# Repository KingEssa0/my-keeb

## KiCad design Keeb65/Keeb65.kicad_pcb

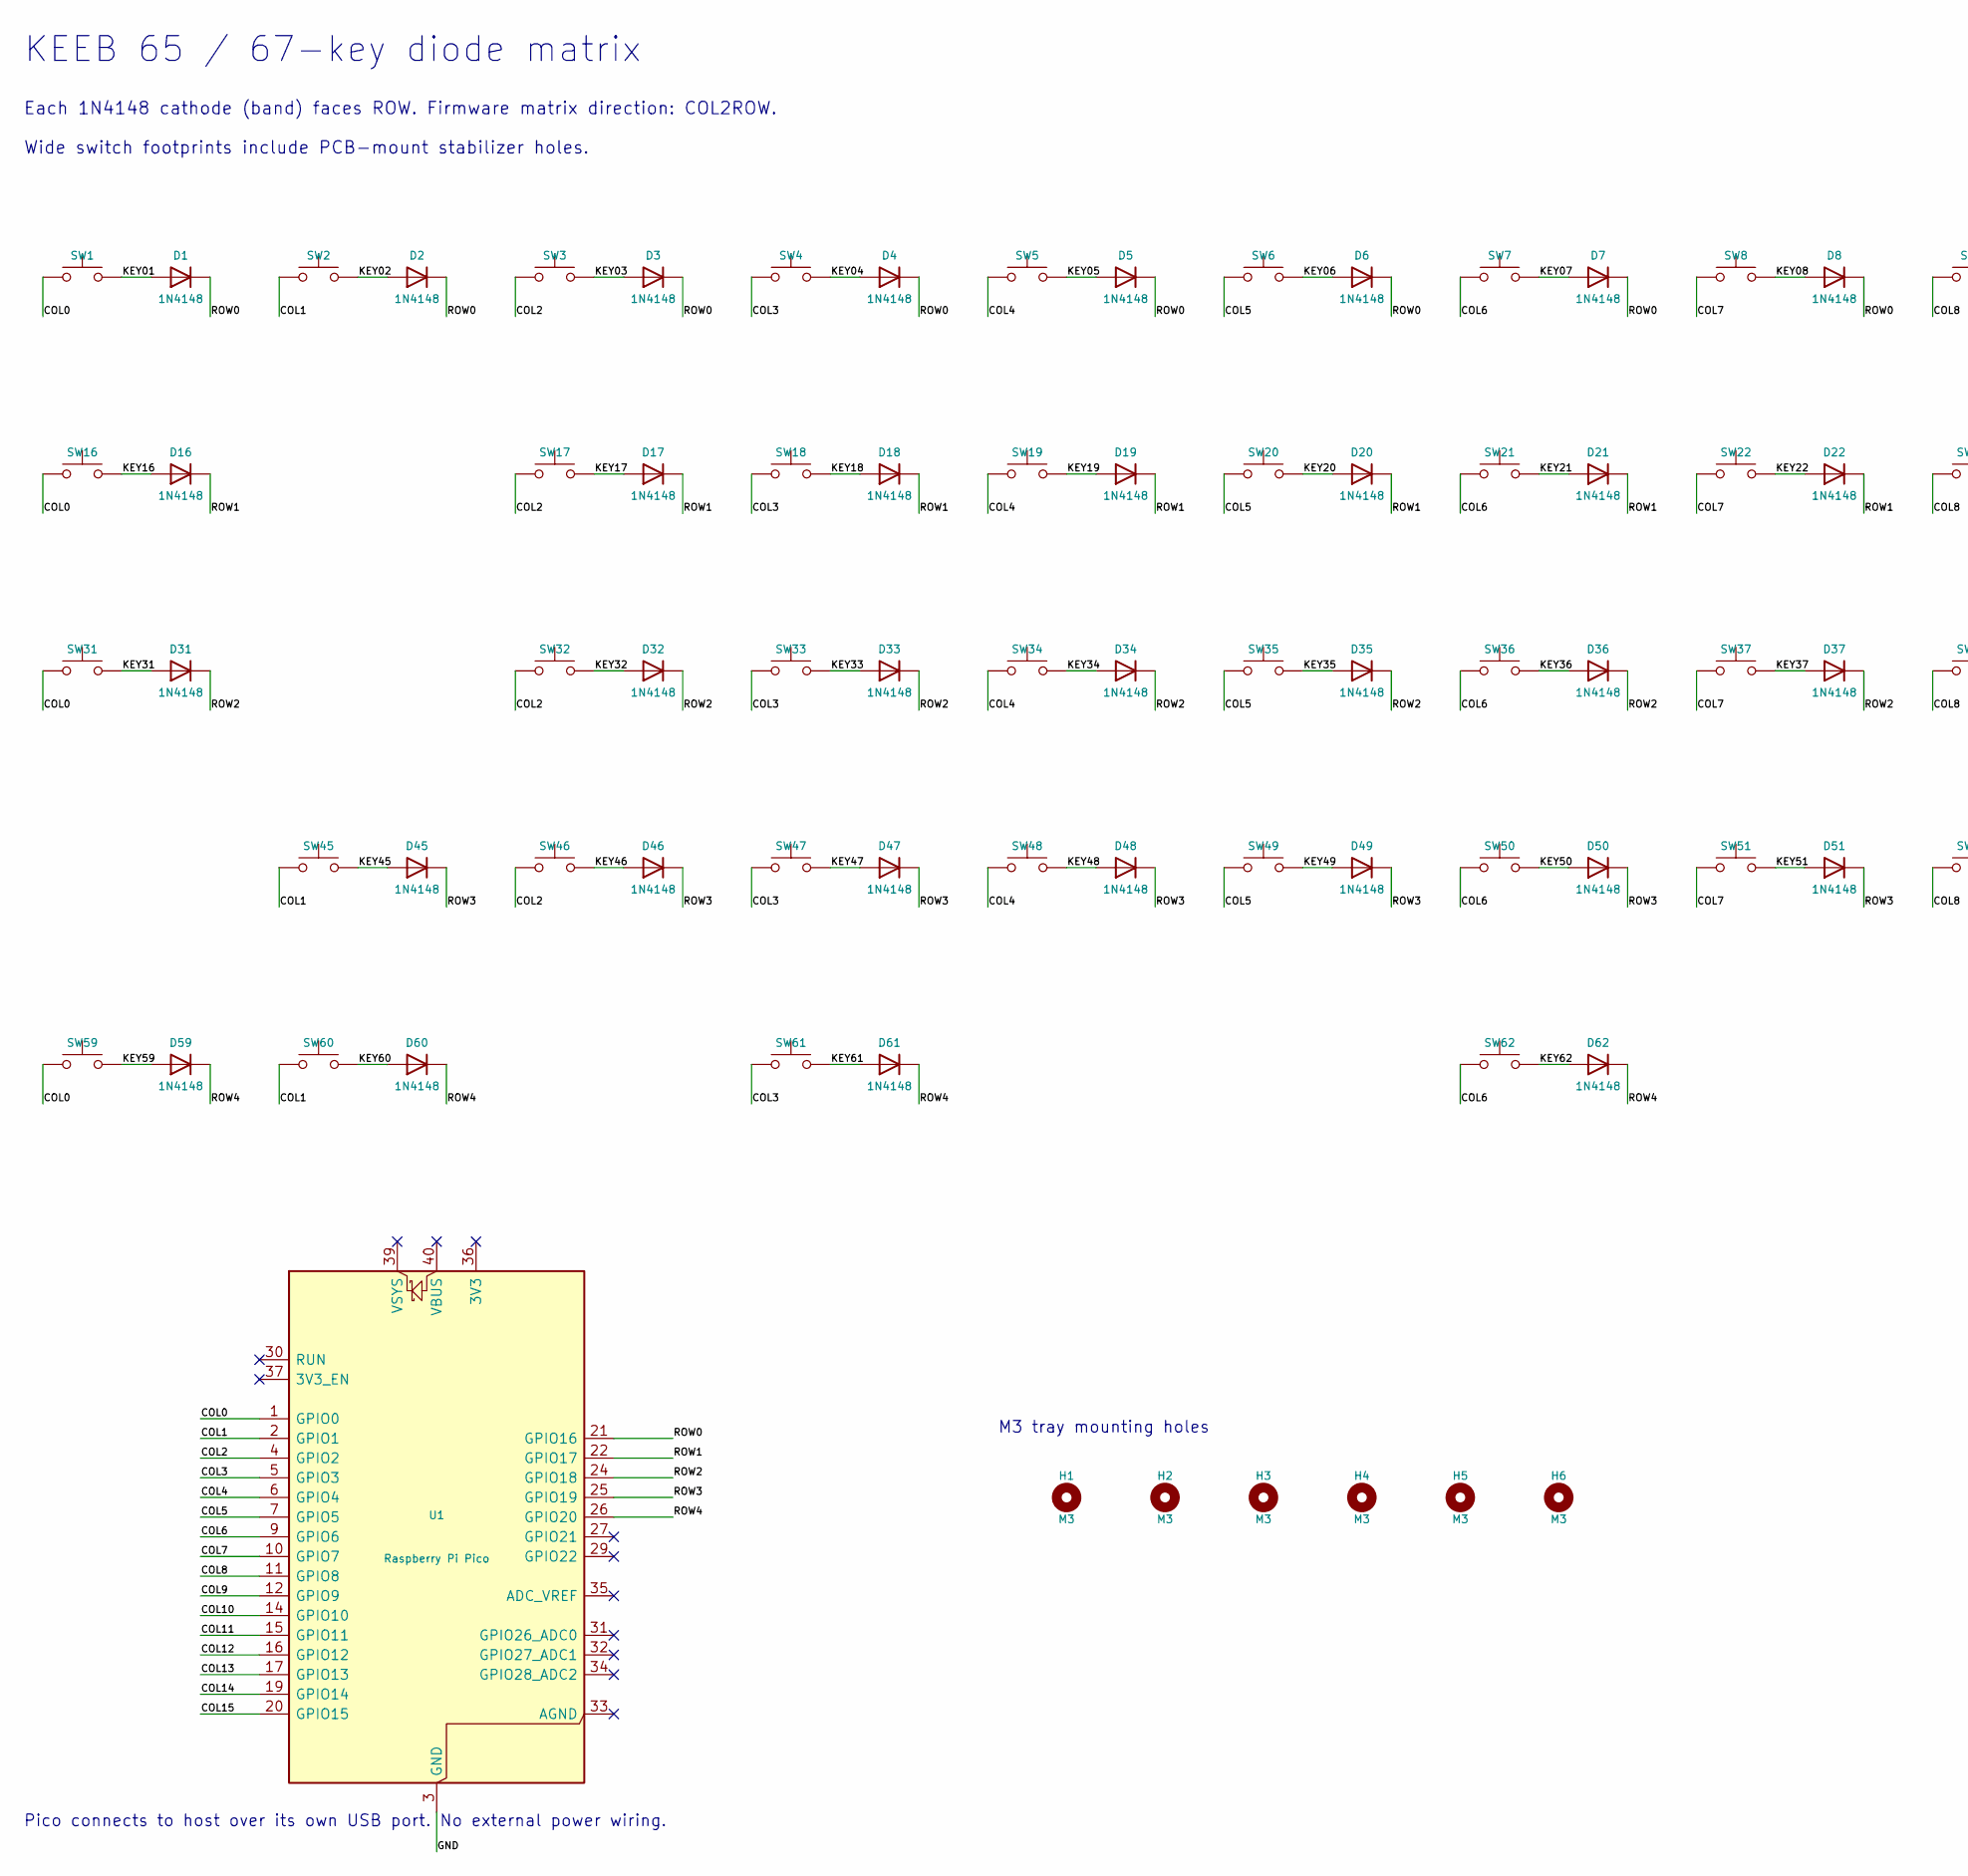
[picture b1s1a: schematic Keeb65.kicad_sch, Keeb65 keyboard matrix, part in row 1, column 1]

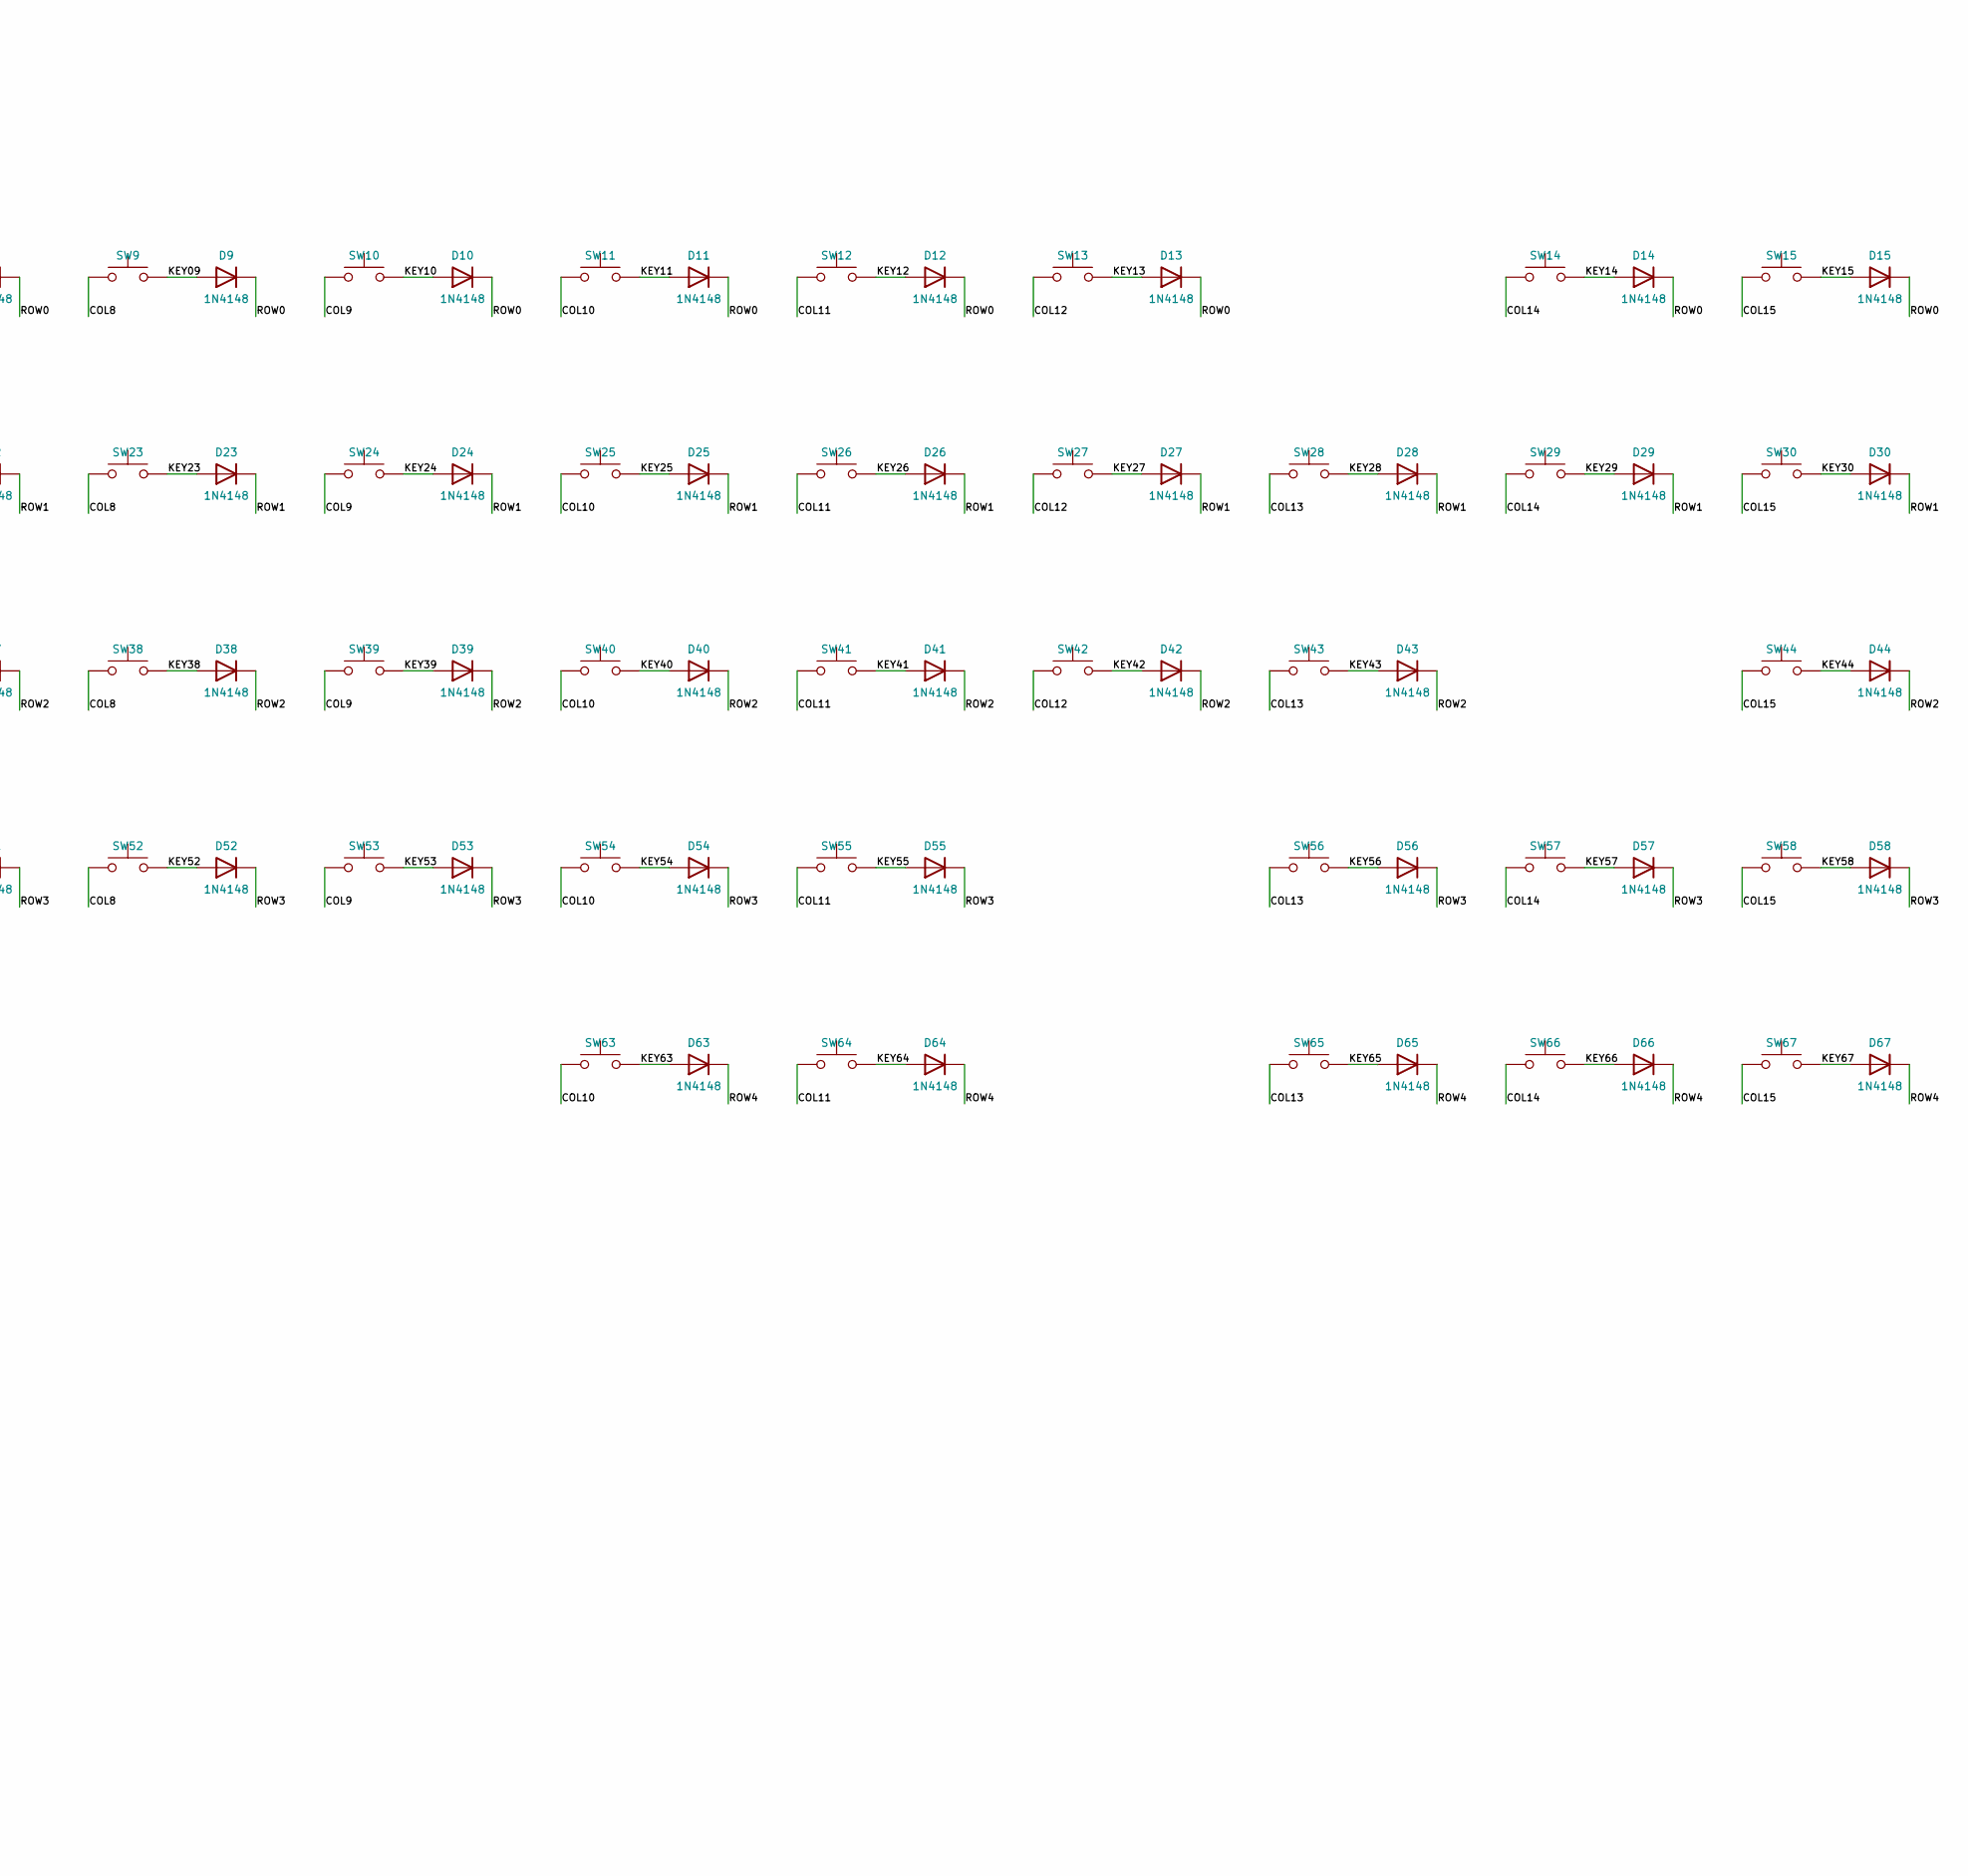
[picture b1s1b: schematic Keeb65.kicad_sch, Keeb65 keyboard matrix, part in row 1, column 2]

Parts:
D1, D2, D3, D4, D5, D6, D7, D8, D9, D10, D11, D12, D13, D14, D15, D16, D17, D18, D19, D20, D21, D22, D23, D24, D25, D26, D27, D28, D29, D30, D31, D32, D33, D34, D35, D36, D37, D38, D39, D40, D41, D42, D43, D44, D45, D46, D47, D48, D49, D50, D51, D52, D53, D54, D55, D56, D57, D58, D59, D60, D61, D62, D63, D64, D65, D66, D67: 1N4148; D_DO-35_SOD27_P7.62mm_Horizontal
H1, H2, H3, H4, H5, H6: M3; MountingHole_3.2mm_M3
SW1: Esc; SW_Cherry_MX_1.00u_PCB
SW2: 1; SW_Cherry_MX_1.00u_PCB
SW3: 2; SW_Cherry_MX_1.00u_PCB
SW4: 3; SW_Cherry_MX_1.00u_PCB
SW5: 4; SW_Cherry_MX_1.00u_PCB
SW6: 5; SW_Cherry_MX_1.00u_PCB
SW7: 6; SW_Cherry_MX_1.00u_PCB
SW8: 7; SW_Cherry_MX_1.00u_PCB
SW9: 8; SW_Cherry_MX_1.00u_PCB
SW10: 9; SW_Cherry_MX_1.00u_PCB
SW11: 0; SW_Cherry_MX_1.00u_PCB
SW12: -; SW_Cherry_MX_1.00u_PCB
SW13: =; SW_Cherry_MX_1.00u_PCB
SW14: Backspace; SW_Cherry_MX_2.00u_PCB
SW15: Del; SW_Cherry_MX_1.00u_PCB
SW16: Tab; SW_Cherry_MX_1.00u_PCB
SW17: Q; SW_Cherry_MX_1.00u_PCB
SW18: W; SW_Cherry_MX_1.00u_PCB
SW19: E; SW_Cherry_MX_1.00u_PCB
SW20: R; SW_Cherry_MX_1.00u_PCB
SW21: T; SW_Cherry_MX_1.00u_PCB
SW22: Y; SW_Cherry_MX_1.00u_PCB
SW23: U; SW_Cherry_MX_1.00u_PCB
SW24: I; SW_Cherry_MX_1.00u_PCB
SW25: O; SW_Cherry_MX_1.00u_PCB
SW26: P; SW_Cherry_MX_1.00u_PCB
SW27: [; SW_Cherry_MX_1.00u_PCB
SW28: ]; SW_Cherry_MX_1.00u_PCB
SW29: \; SW_Cherry_MX_1.00u_PCB
SW30: PgUp; SW_Cherry_MX_1.00u_PCB
SW31: Caps; SW_Cherry_MX_1.00u_PCB
SW32: A; SW_Cherry_MX_1.00u_PCB
SW33: S; SW_Cherry_MX_1.00u_PCB
SW34: D; SW_Cherry_MX_1.00u_PCB
SW35: F; SW_Cherry_MX_1.00u_PCB
SW36: G; SW_Cherry_MX_1.00u_PCB
SW37: H; SW_Cherry_MX_1.00u_PCB
SW38: J; SW_Cherry_MX_1.00u_PCB
SW39: K; SW_Cherry_MX_1.00u_PCB
SW40: L; SW_Cherry_MX_1.00u_PCB
SW41: ;; SW_Cherry_MX_1.00u_PCB
SW42: '; SW_Cherry_MX_1.00u_PCB
SW43: Enter; SW_Cherry_MX_2.25u_PCB
SW44: PgDn; SW_Cherry_MX_1.00u_PCB
SW45: LShift; SW_Cherry_MX_2.25u_PCB
SW46: Z; SW_Cherry_MX_1.00u_PCB
SW47: X; SW_Cherry_MX_1.00u_PCB
SW48: C; SW_Cherry_MX_1.00u_PCB
SW49: V; SW_Cherry_MX_1.00u_PCB
SW50: B; SW_Cherry_MX_1.00u_PCB
SW51: N; SW_Cherry_MX_1.00u_PCB
SW52: M; SW_Cherry_MX_1.00u_PCB
SW53: ,; SW_Cherry_MX_1.00u_PCB
SW54: .; SW_Cherry_MX_1.00u_PCB
SW55: /; SW_Cherry_MX_1.00u_PCB
SW56: RShift; SW_Cherry_MX_1.00u_PCB
SW57: Up; SW_Cherry_MX_1.00u_PCB
SW58: End; SW_Cherry_MX_1.00u_PCB
SW59: LCtrl; SW_Cherry_MX_1.00u_PCB
SW60: Win; SW_Cherry_MX_1.00u_PCB
SW61: LAlt; SW_Cherry_MX_1.00u_PCB
SW62: Space; SW_Cherry_MX_6.25u_PCB
SW63: RAlt; SW_Cherry_MX_1.00u_PCB
SW64: Fn; SW_Cherry_MX_1.00u_PCB
SW65: Left; SW_Cherry_MX_1.00u_PCB
SW66: Down; SW_Cherry_MX_1.00u_PCB
SW67: Right; SW_Cherry_MX_1.00u_PCB
U1: Raspberry Pi Pico; RaspberryPi_Pico_RightEdge_THT

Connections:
/COL0: SW1.1, SW16.1, SW31.1, SW59.1, U1.1 (GPIO0)
/COL1: SW2.1, SW45.1, SW60.1, U1.2 (GPIO1)
/COL2: SW3.1, SW17.1, SW32.1, SW46.1, U1.4 (GPIO2)
/COL3: SW4.1, SW18.1, SW33.1, SW47.1, SW61.1, U1.5 (GPIO3)
/COL4: SW5.1, SW19.1, SW34.1, SW48.1, U1.6 (GPIO4)
/COL5: SW6.1, SW20.1, SW35.1, SW49.1, U1.7 (GPIO5)
/COL6: SW7.1, SW21.1, SW36.1, SW50.1, SW62.1, U1.9 (GPIO6)
/COL7: SW8.1, SW22.1, SW37.1, SW51.1, U1.10 (GPIO7)
/COL8: SW9.1, SW23.1, SW38.1, SW52.1, U1.11 (GPIO8)
/COL9: SW10.1, SW24.1, SW39.1, SW53.1, U1.12 (GPIO9)
/COL10: SW11.1, SW25.1, SW40.1, SW54.1, SW63.1, U1.14 (GPIO10)
/COL11: SW12.1, SW26.1, SW41.1, SW55.1, SW64.1, U1.15 (GPIO11)
/COL12: SW13.1, SW27.1, SW42.1, U1.16 (GPIO12)
/COL13: SW28.1, SW43.1, SW56.1, SW65.1, U1.17 (GPIO13)
/COL14: SW14.1, SW29.1, SW57.1, SW66.1, U1.19 (GPIO14)
/COL15: SW15.1, SW30.1, SW44.1, SW58.1, SW67.1, U1.20 (GPIO15)
/GND: U1.3 (GND), U1.8 (GND), U1.13 (GND), U1.18 (GND), U1.23 (GND), U1.28 (GND), U1.38 (GND)
/KEY01: D1.2 (A), SW1.2
/KEY02: D2.2 (A), SW2.2
/KEY03: D3.2 (A), SW3.2
/KEY04: D4.2 (A), SW4.2
/KEY05: D5.2 (A), SW5.2
/KEY06: D6.2 (A), SW6.2
/KEY07: D7.2 (A), SW7.2
/KEY08: D8.2 (A), SW8.2
/KEY09: D9.2 (A), SW9.2
/KEY10: D10.2 (A), SW10.2
/KEY11: D11.2 (A), SW11.2
/KEY12: D12.2 (A), SW12.2
/KEY13: D13.2 (A), SW13.2
/KEY14: D14.2 (A), SW14.2
/KEY15: D15.2 (A), SW15.2
/KEY16: D16.2 (A), SW16.2
/KEY17: D17.2 (A), SW17.2
/KEY18: D18.2 (A), SW18.2
/KEY19: D19.2 (A), SW19.2
/KEY20: D20.2 (A), SW20.2
/KEY21: D21.2 (A), SW21.2
/KEY22: D22.2 (A), SW22.2
/KEY23: D23.2 (A), SW23.2
/KEY24: D24.2 (A), SW24.2
/KEY25: D25.2 (A), SW25.2
/KEY26: D26.2 (A), SW26.2
/KEY27: D27.2 (A), SW27.2
/KEY28: D28.2 (A), SW28.2
/KEY29: D29.2 (A), SW29.2
/KEY30: D30.2 (A), SW30.2
/KEY31: D31.2 (A), SW31.2
/KEY32: D32.2 (A), SW32.2
/KEY33: D33.2 (A), SW33.2
/KEY34: D34.2 (A), SW34.2
/KEY35: D35.2 (A), SW35.2
/KEY36: D36.2 (A), SW36.2
/KEY37: D37.2 (A), SW37.2
/KEY38: D38.2 (A), SW38.2
/KEY39: D39.2 (A), SW39.2
/KEY40: D40.2 (A), SW40.2
/KEY41: D41.2 (A), SW41.2
/KEY42: D42.2 (A), SW42.2
/KEY43: D43.2 (A), SW43.2
/KEY44: D44.2 (A), SW44.2
/KEY45: D45.2 (A), SW45.2
/KEY46: D46.2 (A), SW46.2
/KEY47: D47.2 (A), SW47.2
/KEY48: D48.2 (A), SW48.2
/KEY49: D49.2 (A), SW49.2
/KEY50: D50.2 (A), SW50.2
/KEY51: D51.2 (A), SW51.2
/KEY52: D52.2 (A), SW52.2
/KEY53: D53.2 (A), SW53.2
/KEY54: D54.2 (A), SW54.2
/KEY55: D55.2 (A), SW55.2
/KEY56: D56.2 (A), SW56.2
/KEY57: D57.2 (A), SW57.2
/KEY58: D58.2 (A), SW58.2
/KEY59: D59.2 (A), SW59.2
/KEY60: D60.2 (A), SW60.2
/KEY61: D61.2 (A), SW61.2
/KEY62: D62.2 (A), SW62.2
/KEY63: D63.2 (A), SW63.2
/KEY64: D64.2 (A), SW64.2
/KEY65: D65.2 (A), SW65.2
/KEY66: D66.2 (A), SW66.2
/KEY67: D67.2 (A), SW67.2
/ROW0: D1.1 (K), D2.1 (K), D3.1 (K), D4.1 (K), D5.1 (K), D6.1 (K), D7.1 (K), D8.1 (K), D9.1 (K), D10.1 (K), D11.1 (K), D12.1 (K), D13.1 (K), D14.1 (K), D15.1 (K), U1.21 (GPIO16)
/ROW1: D16.1 (K), D17.1 (K), D18.1 (K), D19.1 (K), D20.1 (K), D21.1 (K), D22.1 (K), D23.1 (K), D24.1 (K), D25.1 (K), D26.1 (K), D27.1 (K), D28.1 (K), D29.1 (K), D30.1 (K), U1.22 (GPIO17)
/ROW2: D31.1 (K), D32.1 (K), D33.1 (K), D34.1 (K), D35.1 (K), D36.1 (K), D37.1 (K), D38.1 (K), D39.1 (K), D40.1 (K), D41.1 (K), D42.1 (K), D43.1 (K), D44.1 (K), U1.24 (GPIO18)
/ROW3: D45.1 (K), D46.1 (K), D47.1 (K), D48.1 (K), D49.1 (K), D50.1 (K), D51.1 (K), D52.1 (K), D53.1 (K), D54.1 (K), D55.1 (K), D56.1 (K), D57.1 (K), D58.1 (K), U1.25 (GPIO19)
/ROW4: D59.1 (K), D60.1 (K), D61.1 (K), D62.1 (K), D63.1 (K), D64.1 (K), D65.1 (K), D66.1 (K), D67.1 (K), U1.26 (GPIO20)

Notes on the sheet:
KEEB 65 / 67-key diode matrix
Each 1N4148 cathode (band) faces ROW. Firmware matrix direction: COL2ROW.
Wide switch footprints include PCB-mount stabilizer holes.
M3 tray mounting holes
Pico connects to host over its own USB port. No external power wiring.

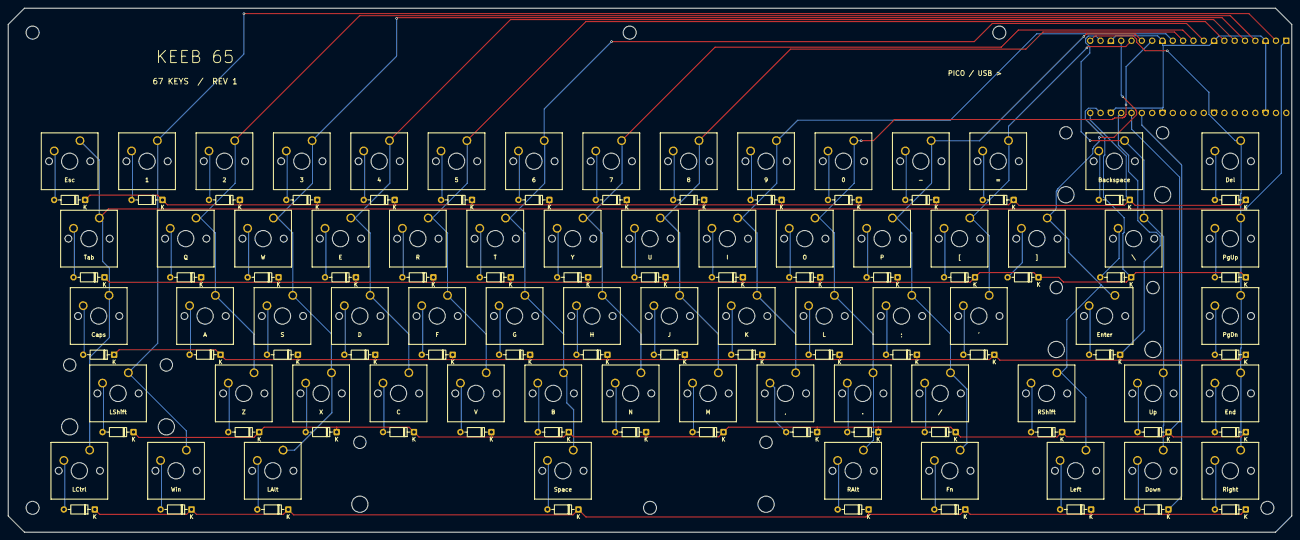
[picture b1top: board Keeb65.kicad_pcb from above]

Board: 2 copper layers, 316.0 x 129.0 mm, 141 parts (0 on the bottom side), 89 nets.

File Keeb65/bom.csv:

Quantity,Part,Notes
1,Raspberry Pi Pico (RP2040),"Original Pico, with micro USB"
2,1x20 2.54 mm male header,Solder Pico to carrier PCB
67,MX-style mechanical switch,"Through-hole, PCB mount"
67,1N4148,"Through-hole DO-35, 7.62 mm lead spacing"
3,2u PCB-mount stabilizer,"Backspace, Enter, and left Shift"
1,6.25u PCB-mount stabilizer,Spacebar
1,65% ANSI MX-compatible keycap set,"Includes 1.75u right Shift, 1.25u bottom modifiers, and 6.25u spacebar"
